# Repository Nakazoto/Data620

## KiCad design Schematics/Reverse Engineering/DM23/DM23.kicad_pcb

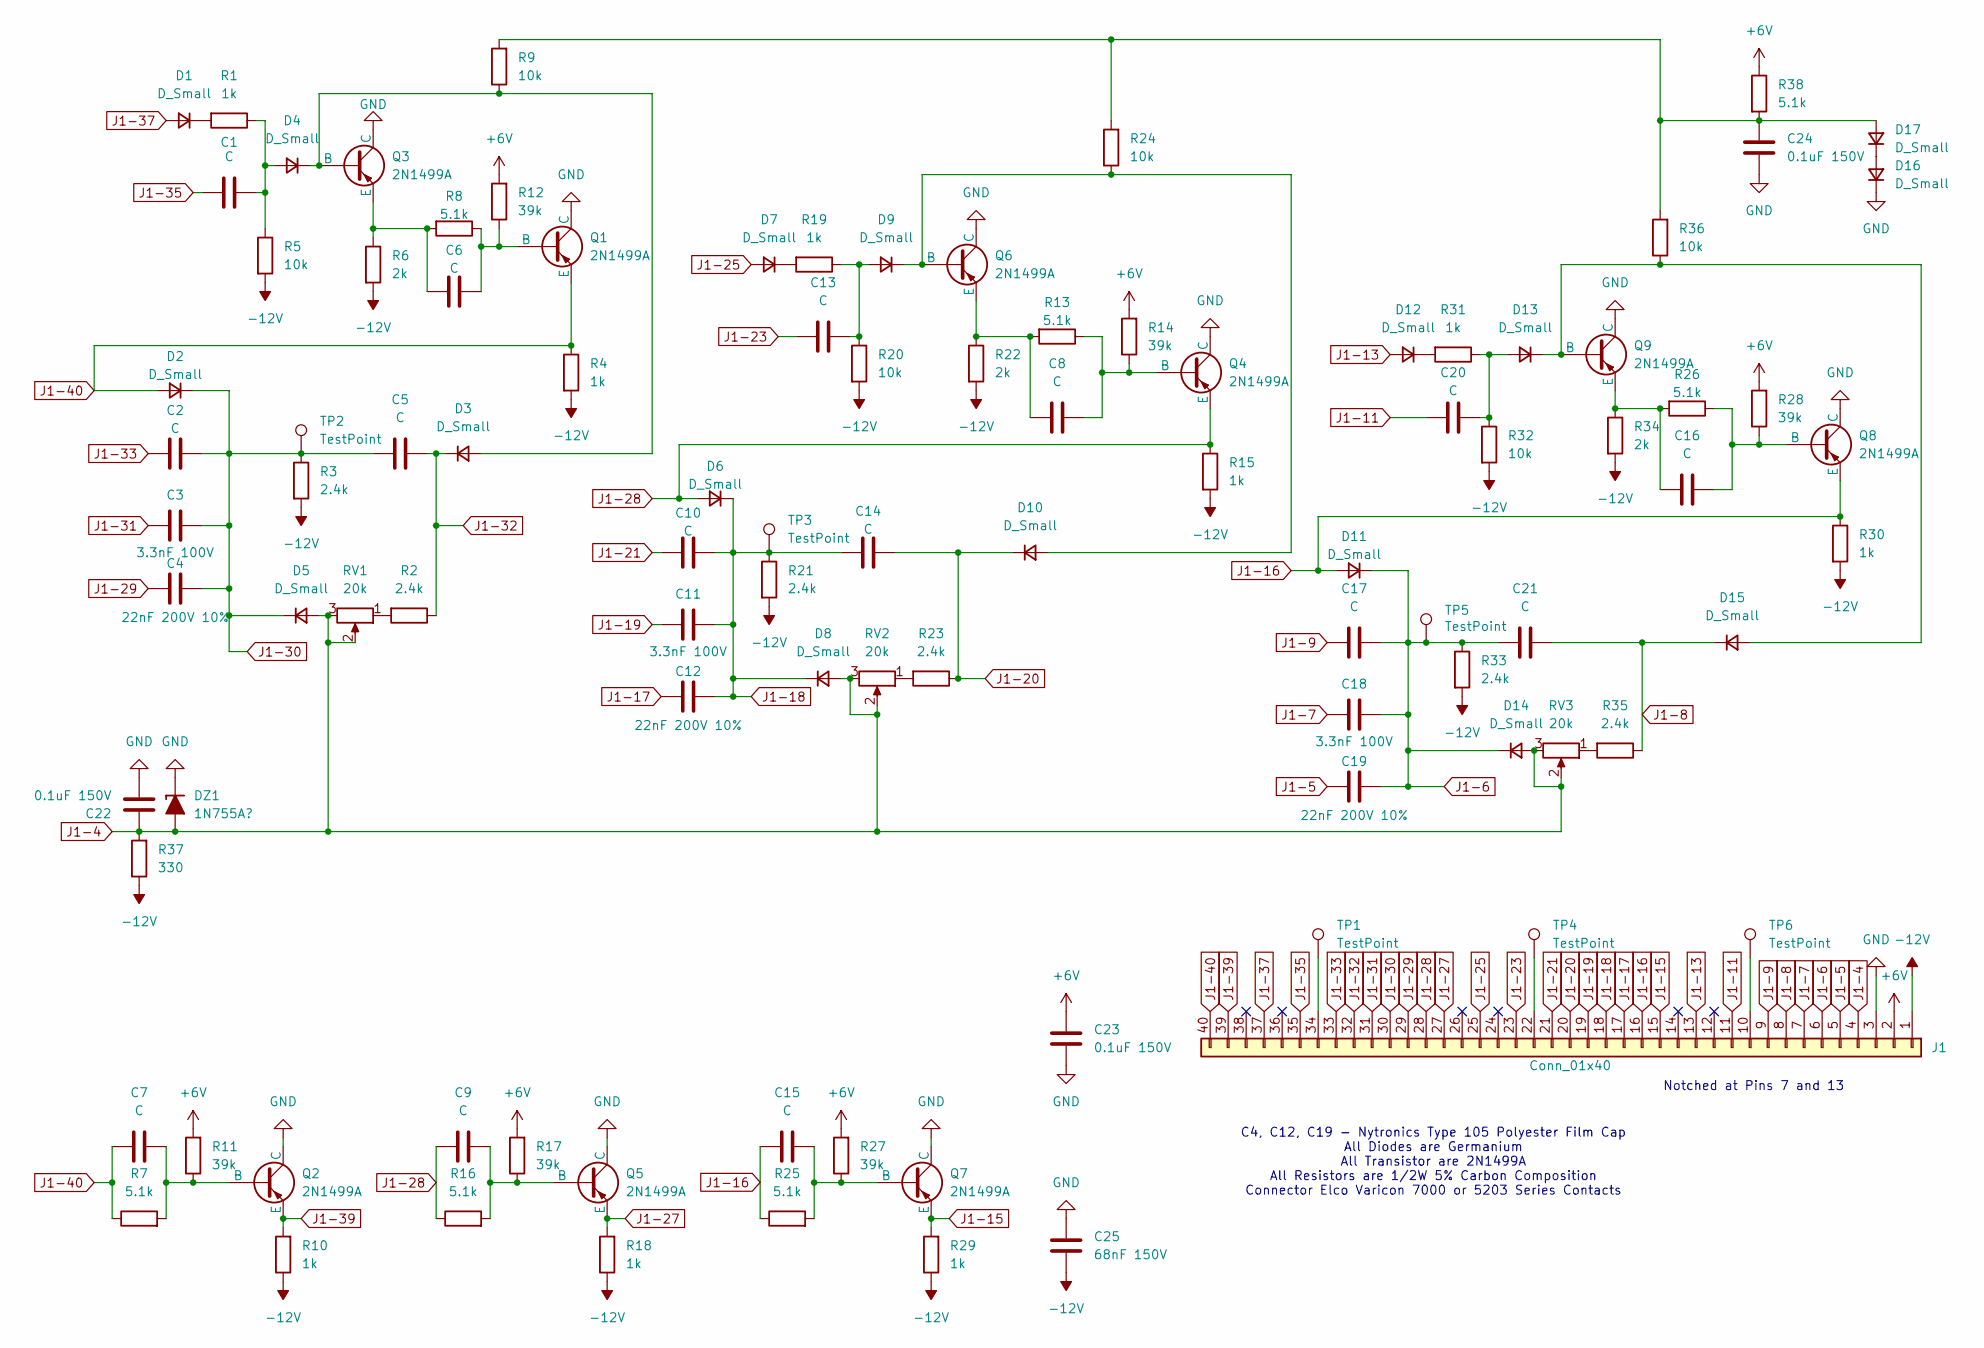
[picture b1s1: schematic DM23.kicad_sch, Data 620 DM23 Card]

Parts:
C1, C2, C5, C6, C7, C8, C9, C10, C13, C14, C15, C16, C17, C20, C21: C; C_Rect_L9.0mm_W2.5mm_P7.50mm_MKT
C3, C11, C18: 3.3nF 100V; CP_Axial_L10.0mm_D4.5mm_P15.00mm_Horizontal
C4, C12, C19: 22nF 200V 10%; CP_Axial_L11.0mm_D5.0mm_P18.00mm_Horizontal
C22, C23, C24: 0.1uF 150V; C_Axial_L5.1mm_D3.1mm_P15.00mm_Horizontal
C25: 68nF 150V; CP_Axial_L11.0mm_D6.0mm_P18.00mm_Horizontal
D1, D2, D3, D4, D5, D6, D7, D8, D9, D10, D11, D12, D13, D14, D15, D16, D17: D_Small; D_A-405_P12.70mm_Horizontal
DZ1: 1N755A?; D_A-405_P12.70mm_Horizontal
J1: Conn_01x40; ELCO 40
Q1, Q2, Q3, Q4, Q5, Q6, Q7, Q8, Q9: 2N1499A; TO-39-3
R1, R4, R10, R15, R18, R19, R29, R30, R31: 1k; R_Axial_DIN0309_L9.0mm_D3.2mm_P15.24mm_Horizontal
R2, R3, R21, R23, R33, R35: 2.4k; R_Axial_DIN0309_L9.0mm_D3.2mm_P15.24mm_Horizontal
R5, R9, R20, R24, R32, R36: 10k; R_Axial_DIN0309_L9.0mm_D3.2mm_P15.24mm_Horizontal
R6, R22, R34: 2k; R_Axial_DIN0309_L9.0mm_D3.2mm_P15.24mm_Horizontal
R7, R8, R13, R16, R25, R26, R38: 5.1k; R_Axial_DIN0309_L9.0mm_D3.2mm_P15.24mm_Horizontal
R11, R12, R14, R17, R27, R28: 39k; R_Axial_DIN0309_L9.0mm_D3.2mm_P15.24mm_Horizontal
R37: 330; R_Axial_DIN0309_L9.0mm_D3.2mm_P15.24mm_Horizontal
RV1, RV2, RV3: 20k; Potentiometer_Bourns_3006W_Horizontal
TP1, TP2, TP3, TP4, TP5, TP6: TestPoint; TestPoint_Keystone_5000-5004_Miniature

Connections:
+6V: C23.2, J1.2, R11.2, R12.2, R14.2, R17.2, R27.2, R28.2, R38.1
-12V: C25.2, J1.1, R3.2, R4.2, R5.2, R6.2, R10.1, R15.2, R18.1, R20.2, R21.2, R22.2, R29.1, R30.2, R32.2, R33.2, R34.2, R37.1
GND: C22.1, C23.1, C24.1, C25.1, D16.1 (K), DZ1.1 (K), J1.3, Q1.1 (C), Q2.1 (C), Q3.1 (C), Q4.1 (C), Q5.1 (C), Q6.1 (C), Q7.1 (C), Q8.1 (C), Q9.1 (C)
J1-4: C22.2, D5.2 (A), D8.2 (A), D14.2 (A), DZ1.2 (A), J1.4, R37.2, RV1.2, RV1.3, RV2.2, RV2.3, RV3.2, RV3.3
J1-5: C19.2, J1.5
J1-6: C17.2, C18.1, C19.1, C21.2, D11.1 (K), D14.1 (K), J1.6, R33.1, TP5.1
J1-7: C18.2, J1.7
J1-8: C21.1, D15.1 (K), J1.8, R35.1
J1-9: C17.1, J1.9
J1-11: C20.1, J1.11
J1-13: D12.2 (A), J1.13
J1-15: J1.15, Q7.3 (E), R29.2
J1-16: C15.1, D11.2 (A), J1.16, Q8.3 (E), R25.1, R30.1
J1-17: C12.2, J1.17
J1-18: C10.2, C11.1, C12.1, C14.2, D6.1 (K), D8.1 (K), J1.18, R21.1, TP3.1
J1-19: C11.2, J1.19
J1-20: C14.1, D10.1 (K), J1.20, R23.1
J1-21: C10.1, J1.21
J1-23: C13.1, J1.23
J1-25: D7.2 (A), J1.25
J1-27: J1.27, Q5.3 (E), R18.2
J1-28: C9.1, D6.2 (A), J1.28, Q4.3 (E), R15.1, R16.1
J1-29: C4.2, J1.29
J1-30: C2.2, C3.1, C4.1, C5.2, D2.1 (K), D5.1 (K), J1.30, R3.1, TP2.1
J1-31: C3.2, J1.31
J1-32: C5.1, D3.1 (K), J1.32, R2.1
J1-33: C2.1, J1.33
J1-35: C1.1, J1.35
J1-37: D1.2 (A), J1.37
J1-39: J1.39, Q2.3 (E), R10.2
J1-40: C7.1, D2.2 (A), J1.40, Q1.3 (E), R4.1, R7.1
unnamed: D1.1 (K), R1.2
unnamed: D3.2 (A), D4.1 (K), Q3.2 (B), R9.1
unnamed: C1.2, D4.2 (A), R1.1, R5.1
unnamed: D7.1 (K), R19.2
unnamed: C13.2, D9.2 (A), R19.1, R20.1
unnamed: D9.1 (K), D10.2 (A), Q6.2 (B), R24.1
unnamed: D12.1 (K), R31.2
unnamed: C20.2, D13.2 (A), R31.1, R32.1
unnamed: D13.1 (K), D15.2 (A), Q9.2 (B), R36.1
unnamed: D16.2 (A), D17.1 (K)
unnamed: C24.2, D17.2 (A), R9.2, R24.2, R36.2, R38.2
unnamed: J1.10, TP6.1
unnamed: J1.22, TP4.1
unnamed: J1.34, TP1.1
unnamed: C6.1, Q1.2 (B), R8.1, R12.1
unnamed: C7.2, Q2.2 (B), R7.2, R11.1
unnamed: C6.2, Q3.3 (E), R6.1, R8.2
unnamed: C8.1, Q4.2 (B), R13.1, R14.1
unnamed: C9.2, Q5.2 (B), R16.2, R17.1
unnamed: C8.2, Q6.3 (E), R13.2, R22.1
unnamed: C15.2, Q7.2 (B), R25.2, R27.1
unnamed: C16.1, Q8.2 (B), R26.1, R28.1
unnamed: C16.2, Q9.3 (E), R26.2, R34.1
unnamed: R2.2, RV1.1
unnamed: R23.2, RV2.1
unnamed: R35.2, RV3.1

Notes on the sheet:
Notched at Pins 7 and 13
C4, C12, C19 - Nytronics Type 105 Polyester Film Cap All Diodes are Germanium All Transistor are 2N1499A All Resistors are 1/2W 5% Carbon Composition Connector Elco Varicon 7000 or 5203 Series Contacts

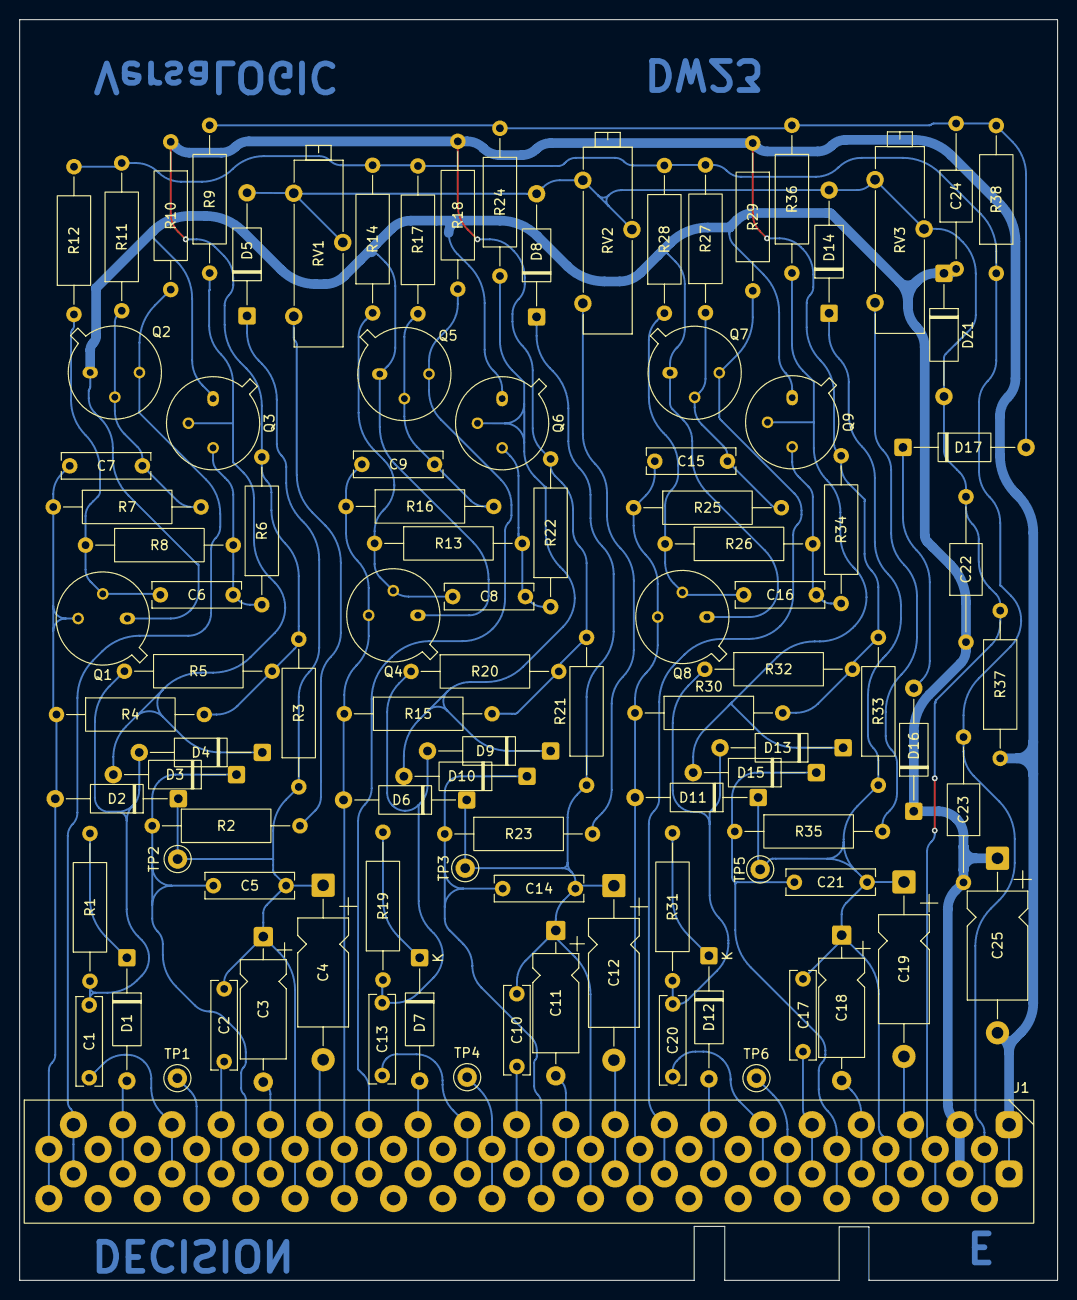
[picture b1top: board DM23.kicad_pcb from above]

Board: 2 copper layers, 107.1 x 130.1 mm, 100 parts (0 on the bottom side), 57 nets.
